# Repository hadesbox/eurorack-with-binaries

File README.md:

# DISCLAIMER!

If you are looking for updated binaries for MI eurorack modules, you should not look into this repo. Most of the binaries are very outdated or even broken who knows ;), so instead use the wonderfull [John Pallister](https://docs.google.com/spreadsheets/d/1KZltEM_g_yhMPhuGk-p82fb1sggsvi72b_s4ztzFu-s/edit#gid=0) spreadsheet.

This repo is mean as guide to understand how to configure files like avrlib/makefile.mk, avrlibx/config.mk, stmlib/makefile.inc in order to compile and develop your own MI variants.

=======
# eurorack-with-binaries

This is a mirror repo of the Mutable Instrumetns Eurorack repo, but additionally it contains under the folder BUILD all the latest compiled programs for the modules (including some WAVs).

The reason why I pushed this repo was to provide compiled programs, since Its not super easy to setup all the libraries and binding in some platform (i.e. OSX), because I tried my self. I was quite easy on Ubuntu, so I pushed all this compiled programs for my personal use (and to share them).

=======

# Uploading
(From [flocked](http://mutable-instruments.net/forum/discussion/4344/mac-tutorial-how-to-compile-and-upload-the-firmware-of-mis-eurorack-modules/p1))

There are three ways of uploading a firmware to the modules:

1. Audio input via wav file (very slow, but no programmer is needed and it’s supported by every module, in order to use this method you must already have the "YOURMODULE_bootloader" into the microcontroller, so a blank *new* microcontroller cannot use this method).
2. FTDI (slower than JTAG, but the programmer isn’t as expensive; 10-15$; Yarns has no FTDI port)
3. JTAG (fast, but the programmer is expensive; 50-60$)

## FTDI

If you want to upload a firmware via FTDI, you will need to get an FTDI programmer. I can recommend FTDI friend (you will need to cut the connection between the two 5v VCC pads and solder the pads for 3v). There are a few additional first steps, before you can compile and upload code via FTDI:

1. Download and install FTDI driver
2. Download Pyserial and unpack the tar.gz
3. Open Terminal and enter:
..* cd /PATHTOPYSERIALFOLDER/
..* sudo python setup.py install
..* Enter: ls /dev/cu.*
4. Copy the returned value that looks similar to: /dev/cu.usbserial-XXXX
8. Open /eurorack/stmlib/makefile.inc
9. Paste the copied value to PGM_SERIAL_PORT

Now you can upload via FTDI:

1. Connect FTDI friend to the 6 FTDI pins on your module (the module needs to be connected to your eurorack busboard for power).
2. Press and hold RESET. Press SYSBOOT simultaneously, then release reset while still holding SYSBOOT.
3. Open Terminal and enter: “cd /PATHTOEURORACKFOLDER/”
4. To upload: “make -f /MODULENAME/makefile upload_combo_serial”

# Libraries and configuration

Remember you will have to probably change some configuration on your computer, since avrlib, avrdude and many other tools and libs are installed on different paths on different distros (Win, OSX, Ubuntu, Centos, etc...) here are mine just you can double check yours!

### avrlib/makefile.mk

```
luix@boxita:~/git/eurorack/avrlib$ git diff
diff --git a/makefile.mk b/makefile.mk
index 3c1f5be..7a84990 100644
--- a/makefile.mk
+++ b/makefile.mk
@@ -13,7 +13,7 @@
 # You should have received a copy of the GNU General Public License
 # along with this program.  If not, see <http://www.gnu.org/licenses/>.
 
-AVRLIB_TOOLS_PATH ?= /usr/local/CrossPack-AVR/bin/
+AVRLIB_TOOLS_PATH ?= /usr/bin/
 BUILD_ROOT     = build/
 BUILD_DIR      = $(BUILD_ROOT)$(TARGET)/
 PROGRAMMER     ?= avrispmkI
```

### avrlibx/config.mk

```
luix@boxita:~/git/eurorack/avrlibx$ git diff
diff --git a/config.mk b/config.mk
index d9c0160..0ad41fa 100644
--- a/config.mk
+++ b/config.mk
@@ -13,7 +13,7 @@
 # You should have received a copy of the GNU General Public License
 # along with this program.  If not, see <http://www.gnu.org/licenses/>.
 
-AVRLIBX_TOOLS_PATH = /usr/local/CrossPack-AVR/bin/
-AVRDUDE_PATH       = /usr/local/CrossPack-AVR/bin/
+AVRLIBX_TOOLS_PATH = /usr/bin/
+AVRDUDE_PATH       = /usr/bin/
 PROGRAMMER         = avrispmkII
 PROGRAMMER_PORT    = usb
```

### stmlib/makefile.inc

```
luix@boxita:~/git/eurorack/stmlib$ git diff
diff --git a/makefile.inc b/makefile.inc
index 341bbae..3480e98 100644
--- a/makefile.inc
+++ b/makefile.inc
@@ -26,11 +26,14 @@
 # Files and directories
 # ------------------------------------------------------------------------------
 
-TOOLCHAIN_PATH ?= /usr/local/arm/
+TOOLCHAIN_PATH = /home/luix/apps/gcc/gcc-arm-none-eabi-4_8-2013q4/
 TOOLCHAIN_BIN  = $(TOOLCHAIN_PATH)bin/
 STM32_PATH     = stmlib/third_party/STM
 
-PGM_SERIAL_PORT = /dev/tty.usbserial-A100S09O
+PGM_SERIAL_PORT = /dev/ttyUSB0
 PGM_SERIAL_BAUD_RATE = 115200
 PGM_SERIAL_VERIFY = -v
```

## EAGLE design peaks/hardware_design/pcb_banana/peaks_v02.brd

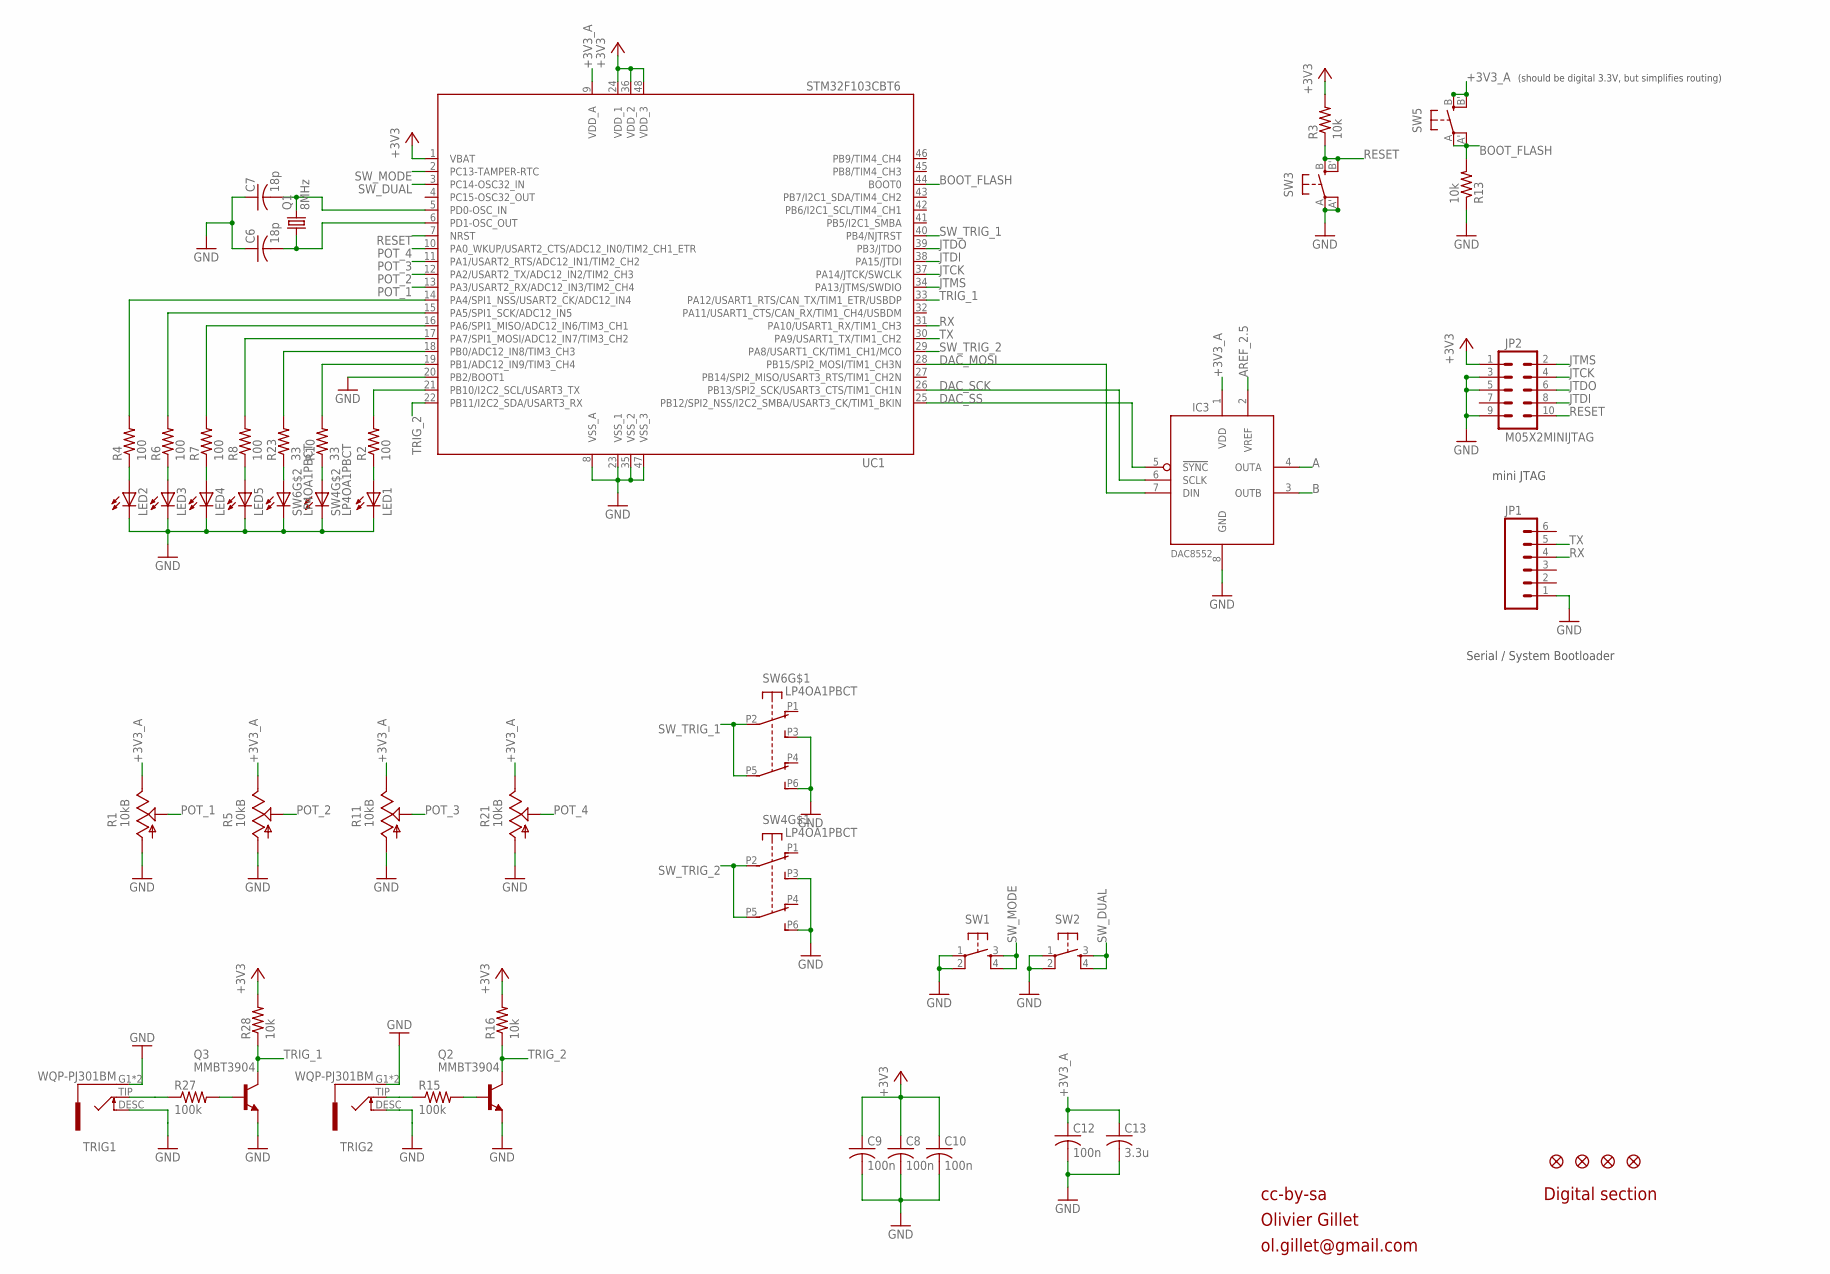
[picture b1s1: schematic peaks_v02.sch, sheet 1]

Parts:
C6, C7: 18p; C0603
C8, C9, C10, C12: 100n; C0603
C13: 3.3u; C0603
F1, F2, F3, F4: FIDUCIAL1X2; FIDUCIAL-1X2
IC3: DAC8552; MSOP-8
JP1: M06SIP; 1X06
JP2: M05X2MINIJTAG; 2X5-1.27
LED1, LED2, LED3, LED4, LED5: LED3MM
Q1: 8MHz; HC49UP
Q2, Q3: MMBT3904; SOT23-BEC
R1, R5, R11, R21: 10kB; ALPS_POT_VERTICAL_PS
R2, R4, R6, R7, R8: 100; R0603
R3, R13, R16, R28: 10k; R0603
R10, R23: 33; R0603
R15, R27: 100k; R0603
SW1, SW2: TAC_SWITCHPTH; TACTILE-PTH
SW3, SW5: EVQQ2; EVQ-Q2
SW4, SW6: LP4OA1PBCT
TRIG1, TRIG2: WQP-PJ301BM
UC1: STM32F103CBT6; LQFP48

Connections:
+3V3: C8.1, C9.1, C10.1, JP2.1, R3.2, R16.2, R28.2, UC1.1 (VBAT), UC1.24 (VDD_1), UC1.36 (VDD_2), UC1.48 (VDD_3); also elsewhere on the board
+3V3_A: C12.1, C13.1, IC3.1 (VDD), R1.P$1 (E), R5.P$1 (E), R11.P$1 (E), R21.P$1 (E), SW5.B (S), SW5.B' (S1), UC1.9 (VDD_A); also elsewhere on the board
A: IC3.4 (OUTA); also elsewhere on the board
AREF_2.5: IC3.2 (VREF); also elsewhere on the board
B: IC3.3 (OUTB); also elsewhere on the board
BOOT_FLASH: R13.2, SW5.A, SW5.A' (P1), UC1.44 (BOOT0)
DAC_MOSI: IC3.7 (DIN), UC1.28 (PB15/SPI2_MOSI/TIM1_CH3N)
DAC_SCK: IC3.6 (SCLK), UC1.26 (PB13/SPI2_SCK/USART3_CTS/TIM1_CH1N)
DAC_SS: IC3.5 (!SYNC), UC1.25 (PB12/SPI2_NSS/I2C2_SMBA/USART3_CK/TIM1_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)
GND: C6.1, C7.1, C8.2, C9.2, C10.2, C12.2, C13.2, IC3.8 (GND), JP1.1, JP2.3, JP2.5, JP2.9, LED1.K (C), LED2.K (C), LED3.K (C), LED4.K (C), LED5.K (C), Q2.E, Q3.E, R1.P$3 (A), R5.P$3 (A), R11.P$3 (A), R13.1, R21.P$3 (A), SW1.1, SW1.2, SW2.1, SW2.2, SW3.A, SW3.A' (P1), SW4.L2, SW4.P3 (A3), SW4.P6 (B3), SW6.L2, SW6.P3 (A3), SW6.P6 (B3), TRIG1.DESC (SWITCH), TRIG1.G1 (SLEVE), TRIG1.G2 (SLEVE), TRIG2.DESC (SWITCH), TRIG2.G1 (SLEVE), TRIG2.G2 (SLEVE), UC1.8 (VSS_A), UC1.20 (PB2/BOOT1), UC1.23 (VSS_1), UC1.35 (VSS_2), UC1.47 (VSS_3); also elsewhere on the board
JTCK: JP2.4, UC1.37 (PA14/JTCK/SWCLK)
JTDI: JP2.8, UC1.38 (PA15/JTDI)
JTDO: JP2.6, UC1.39 (PB3/JTDO)
JTMS: JP2.2, UC1.34 (PA13/JTMS/SWDIO)
unnamed: R15.1, TRIG2.TIP
unnamed: R23.2, UC1.18 (PB0/ADC12_IN8/TIM3_CH3)
unnamed: LED2.A, R4.1
unnamed: LED3.A, R6.1
unnamed: LED4.A, R7.1
unnamed: LED5.A, R8.1
unnamed: C7.2, Q1.2, UC1.5 (PD0-OSC_IN)
unnamed: C6.2, Q1.1, UC1.6 (PD1-OSC_OUT)
unnamed: R10.2, UC1.19 (PB1/ADC12_IN9/TIM3_CH4)
unnamed: R4.2, UC1.14 (PA4/SPI1_NSS/USART2_CK/ADC12_IN4)
unnamed: R6.2, UC1.15 (PA5/SPI1_SCK/ADC12_IN5)
unnamed: R7.2, UC1.16 (PA6/SPI1_MISO/ADC12_IN6/TIM3_CH1)
unnamed: R8.2, UC1.17 (PA7/SPI1_MOSI/ADC12_IN7/TIM3_CH2)
unnamed: Q2.B, R15.2
unnamed: R23.1, SW6.L1
unnamed: R10.1, SW4.L1
unnamed: LED1.A, R2.1
unnamed: R2.2, UC1.21 (PB10/I2C2_SCL/USART3_TX)
unnamed: R27.1, TRIG1.TIP
unnamed: Q3.B, R27.2
POT_1: R1.P$2 (S), UC1.13 (PA3/USART2_RX/ADC12_IN3/TIM2_CH4)
POT_2: R5.P$2 (S), UC1.12 (PA2/USART2_TX/ADC12_IN2/TIM2_CH3)
POT_3: R11.P$2 (S), UC1.11 (PA1/USART2_RTS/ADC12_IN1/TIM2_CH2)
POT_4: R21.P$2 (S), UC1.10 (PA0_WKUP/USART2_CTS/ADC12_IN0/TIM2_CH1_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)
RESET: JP2.10, R3.1, SW3.B (S), SW3.B' (S1), UC1.7 (NRST)
RX: JP1.4, UC1.31 (PA10/USART1_RX/TIM1_CH3)
SW_DUAL: SW2.3, SW2.4, UC1.3 (PC14-OSC32_IN)
SW_MODE: SW1.3, SW1.4, UC1.2 (PC13-TAMPER-RTC)
SW_TRIG_1: SW6.P2 (A2), SW6.P5 (B2), UC1.40 (PB4/NJTRST)
SW_TRIG_2: SW4.P2 (A2), SW4.P5 (B2), UC1.29 (PA8/USART1_CK/TIM1_CH1/MCO)
TRIG_1: Q3.C, R28.1, UC1.33 (PA12/USART1_RTS/CAN_TX/TIM1_ETR/USBDP)
TRIG_2: Q2.C, R16.1, UC1.22 (PB11/I2C2_SDA/USART3_RX)
TX: JP1.5, UC1.30 (PA9/USART1_TX/TIM1_CH2)

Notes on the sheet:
cc-by-sa
Olivier Gillet
ol.gillet@gmail.com
Digital section
mini JTAG
Serial / System Bootloader
(should be digital 3.3V, but simplifies routing)

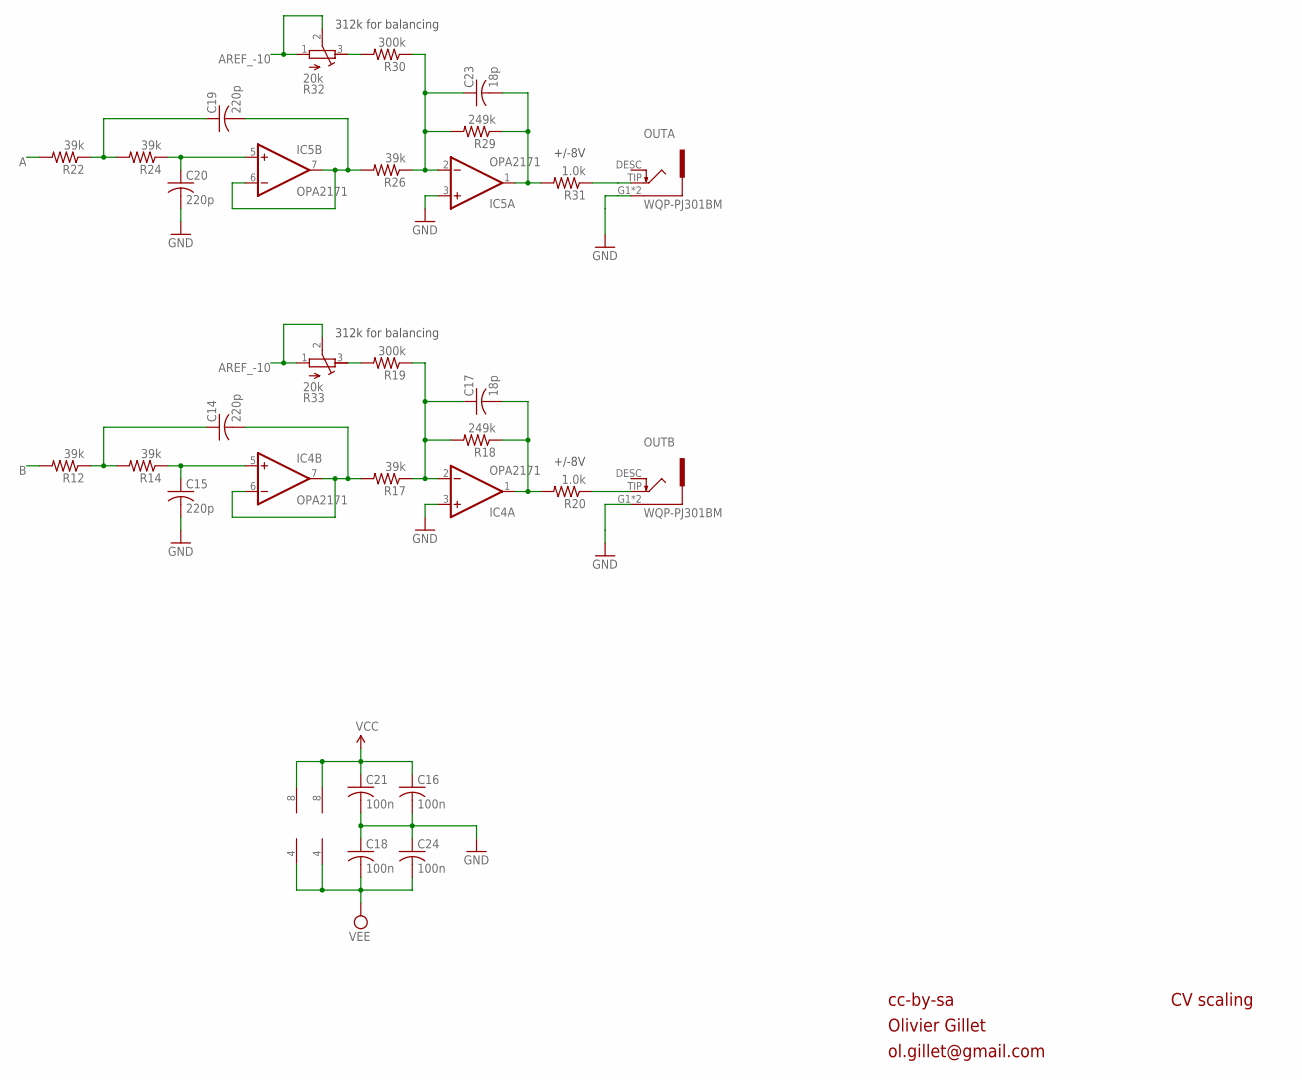
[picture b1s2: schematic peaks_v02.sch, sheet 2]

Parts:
C14, C15, C19, C20: 220p; C0603
C16, C18, C21, C24: 100n; C0603
C17, C23: 18p; C0603
IC4, IC5: OPA2171; SO08
OUTA: WQP-PJ301BM
OUTB: WQP-PJ301BM
R12, R14, R17, R22, R24, R26: 39k; R0603
R18, R29: 249k; R0603
R19, R30: 300k; R0603
R20, R31: 1.0k; R0603
R32, R33: 20k; RTRIM3296W

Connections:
A: R22.2; also elsewhere on the board
AREF_-10: R32.1 (E), R32.2 (S), R33.1 (E), R33.2 (S); also elsewhere on the board
B: R12.2; also elsewhere on the board
BI_OUT: C17.2, IC4.1 (OUT), R18.1, R20.2
BI_OUT1: C23.2, IC5.1 (OUT), R29.1, R31.2
F_CV: C17.1, IC4.2 (-IN), R17.1, R18.2, R19.1
F_CV1: C23.1, IC5.2 (-IN), R26.1, R29.2, R30.1
GND: C15.2, C16.2, C18.1, C20.2, C21.2, C24.1, IC4.3 (+IN), IC5.3 (+IN), OUTA.G1 (SLEVE), OUTA.G2 (SLEVE), OUTB.G1 (SLEVE), OUTB.G2 (SLEVE); also elsewhere on the board
unnamed: C19.2, IC5.6 (-IN), IC5.7 (OUT), R26.2
unnamed: C20.1, IC5.5 (+IN), R24.1
unnamed: C19.1, R22.1, R24.2
unnamed: OUTB.TIP, R20.1
unnamed: R30.2, R32.3 (A)
unnamed: OUTA.TIP, R31.1
unnamed: C14.2, IC4.6 (-IN), IC4.7 (OUT), R17.2
unnamed: C15.1, IC4.5 (+IN), R14.1
unnamed: C14.1, R12.1, R14.2
unnamed: R19.2, R33.3 (A)
VCC: C16.1, C21.1, IC4.8 (V+), IC5.8 (V+); also elsewhere on the board
VEE: C18.2, C24.2, IC4.4 (V-), IC5.4 (V-); also elsewhere on the board

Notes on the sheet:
+/-8V
312k for balancing
cc-by-sa
Olivier Gillet
ol.gillet@gmail.com
CV scaling

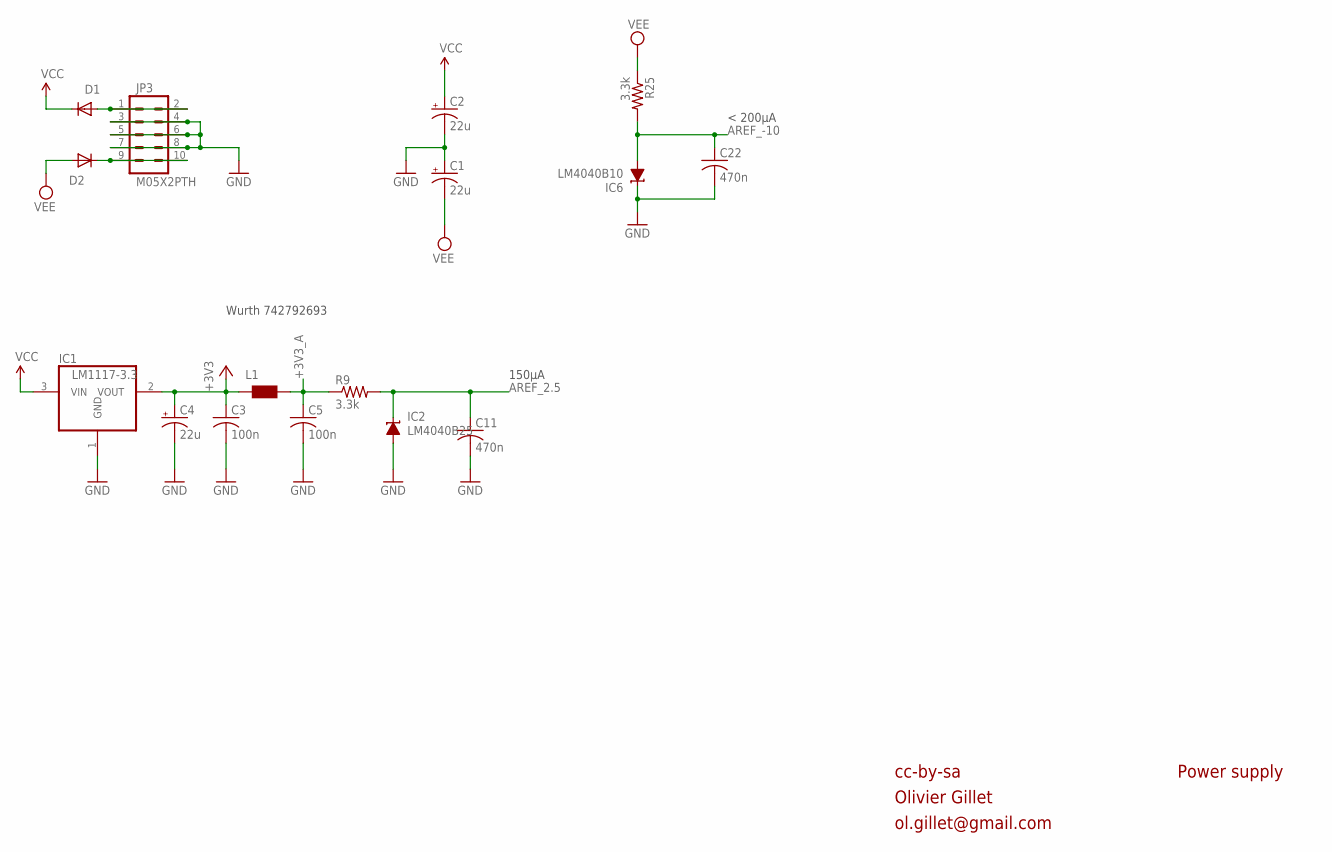
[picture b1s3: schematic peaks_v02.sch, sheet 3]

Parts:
C1, C2, C4: 22u; PANASONIC_C
C3, C5: 100n; C0603
C11, C22: 470n; C0603
D1, D2: 1N5819HW; SOD123
IC1: LM1117-3.3; SOT223
IC2: LM4040B25; DBZ_R-PDSO-G3
IC6: LM4040B10; DBZ_R-PDSO-G3
JP3: M05X2PTH; AVR_ICSP
L1: WE-CBF_0603; 0603
R9, R25: 3.3k; R0603

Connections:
+3V3: C3.1, C4.+, IC1.2 (VOUT), L1.1; also elsewhere on the board
+3V3_A: C5.1, L1.2, R9.1; also elsewhere on the board
AREF_2.5: C11.1, IC2.1 (C), R9.2; also elsewhere on the board
AREF_-10: C22.1, IC6.2 (A), R25.2; also elsewhere on the board
GND: C1.+, C2.-, C3.2, C4.-, C5.2, C11.2, C22.2, IC1.1 (GND), IC2.2 (A), IC6.1 (C), JP3.3, JP3.4, JP3.5, JP3.6, JP3.7, JP3.8; also elsewhere on the board
unnamed: D1.A, JP3.1, JP3.2
unnamed: D2.C, JP3.9, JP3.10
VCC: C2.+, D1.C, IC1.3 (VIN); also elsewhere on the board
VEE: C1.-, D2.A, R25.1; also elsewhere on the board

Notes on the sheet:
cc-by-sa
Olivier Gillet
ol.gillet@gmail.com
Power supply
Wurth 742792693
< 200µA
150µA

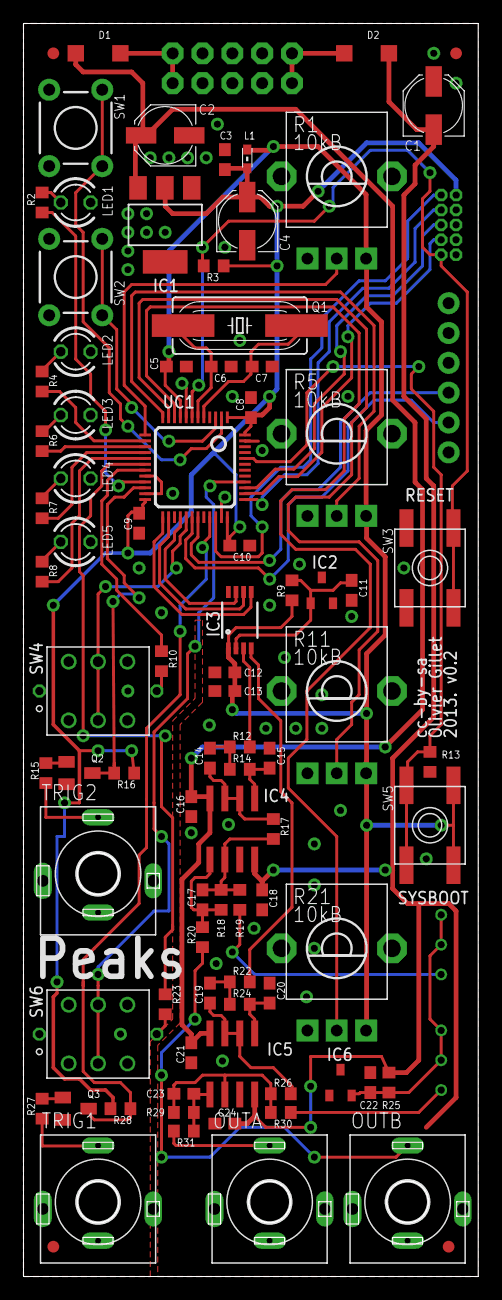
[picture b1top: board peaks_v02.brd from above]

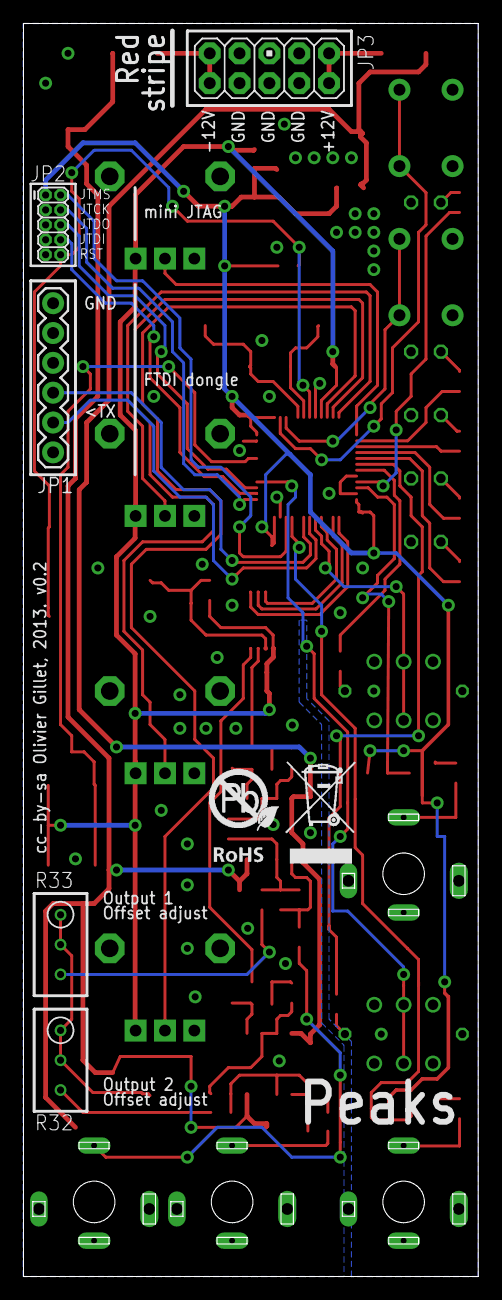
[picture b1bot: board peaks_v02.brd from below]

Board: 2 copper layers, 38.7 x 106.7 mm, 94 parts (6 on the bottom side), 66 nets.

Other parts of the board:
U$1: EURORACK_TEMPLATE
U$2: ROHS

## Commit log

2015-03-18 Adding binaries
2015-03-18 Fix readme
2015-03-18 Adding some
2015-03-18 stuff
2015-03-29 Adding peaks for banana
2015-03-29 adding rapid bananas
2015-04-05 Fixes to peaks bananas
2015-04-13 Adding example config to README.md

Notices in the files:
peaks/hardware_design/pcb_banana/peaks_v02.brd:
cc-by-sa Olivier Gillet, 2013. v0.2
